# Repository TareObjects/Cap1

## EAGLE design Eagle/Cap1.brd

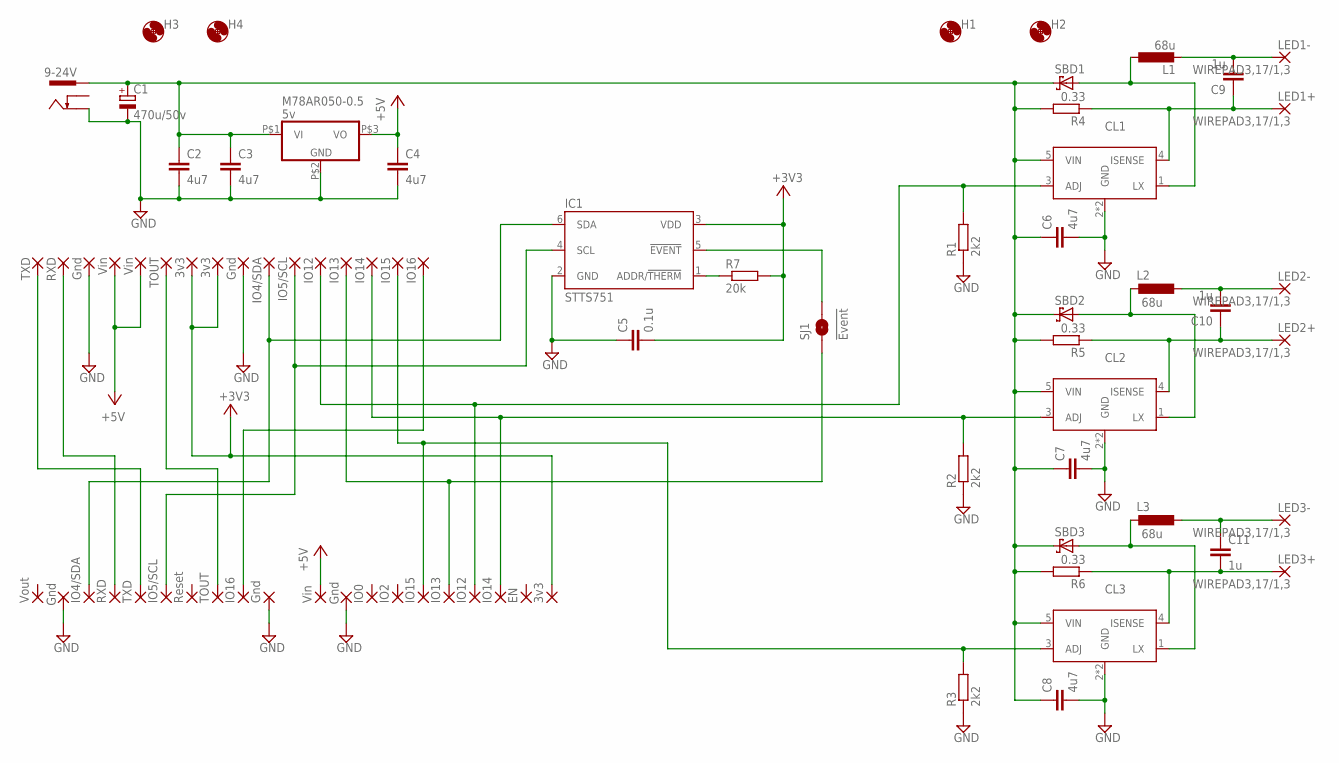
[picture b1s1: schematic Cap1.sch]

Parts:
0: IO0; 1,6/0,8
2: IO2; 1,6/0,8
3V, 3V3, 3V3': 3v3; 1,6/0,8
4: IO4/SDA; 1,6/0,8
5: IO5/SCL; 1,6/0,8
9-24V: DCJACK-MJ179P-R; MJ-179P-R
12: IO12; 1,6/0,8
13: IO13; 1,6/0,8
14: IO14; 1,6/0,8
15: IO15; 1,6/0,8
16: IO16; 1,6/0,8
C1: 470u/50v; E5-13
C2, C3, C4, C6, C7, C8: 4u7; C0805
C5: 0.1u; C0603
C9, C10, C11: 1u; C0603
CL1, CL2, CL3: CL6807; SOT89-5
EN: EN; 1,6/0,8
G: Gnd; 1,6/0,8
G': Gnd; 1,6/0,8
G'': Gnd; 1,6/0,8
GND, GND1: Gnd; 1,6/0,8
H1, H2, H3, H4: MOUNT-HOLE3.0; 3,0
IC1: STTS751; SOT23-6
IO4/SDA: IO4/SDA; 1,6/0,8
IO5/SCL: IO5/SCL; 1,6/0,8
IO12-CH1: IO12; 1,6/0,8
IO13': IO13; 1,6/0,8
IO14-CH2: IO14; 1,6/0,8
IO15-CH3: IO15; 1,6/0,8
IO16: IO16; 1,6/0,8
L1, L2, L3: 68u; NR10050
LED1+, LED1-, LED2+, LED2-, LED3+, LED3-: WIREPAD3,17/1,3; 3,17/1,3
M78AR050-0.5: 5v; M78AR
R1, R2, R3: 2k2; R0603
R4, R5, R6: 0.33; R3225
R7: 20k; R0603
RS: Reset; 1,6/0,8
RX: RXD; 1,6/0,8
RXD: RXD; 1,6/0,8
SBD1, SBD2, SBD3: SS2040FL2SS2040FL; SOD-123FL
SJ1: !Event; SJ_2S-NO
TO: TOUT; 1,6/0,8
TOUT: TOUT; 1,6/0,8
TX: TXD; 1,6/0,8
TXD: TXD; 1,6/0,8
VI: Vin; 1,6/0,8
VIN: Vin; 1,6/0,8
VIN': Vin; 1,6/0,8
VO: Vout; 1,6/0,8

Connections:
24VSUPPLY: 9-24V.1, C1.+, C2.1, C3.1, C6.1, C7.1, C8.1, CL1.5 (VIN), CL2.5 (VIN), CL3.5 (VIN), M78AR050-0.5.P$1 (VI), R4.2, R5.2, R6.2, SBD1.C, SBD2.C, SBD3.C
+3V3: 3V.1, 3V3.1, 3V3'.1, C5.2, IC1.3 (VDD), R7.2
+5V: C4.1, M78AR050-0.5.P$3 (VO), VI.1, VIN.1, VIN'.1
GND: 9-24V.2, C1.-, C2.2, C3.2, C4.2, C5.1, C6.2, C7.2, C8.2, CL1.2 (GND), CL1.2@TAB (GND), CL2.2 (GND), CL2.2@TAB (GND), CL3.2 (GND), CL3.2@TAB (GND), G.1, G'.1, G''.1, GND.1, GND1.1, IC1.2 (GND), M78AR050-0.5.P$2 (GND), R1.1, R2.1, R3.1
unnamed: RX.1, RXD.1
unnamed: TX.1, TXD.1
unnamed: TO.1, TOUT.1
unnamed: 15.1, CL3.3 (ADJ), IO15-CH3.1, R3.2
unnamed: IC1.1 (ADDR/!THERM), R7.1
unnamed: 13.1, IO13'.1, SJ1.1
unnamed: 4.1, IC1.6 (SDA), IO4/SDA.1
unnamed: 5.1, IC1.4 (SCL), IO5/SCL.1
unnamed: IC1.5 (!EVENT), SJ1.2
unnamed: 12.1, CL1.3 (ADJ), IO12-CH1.1, R1.2
unnamed: 14.1, CL2.3 (ADJ), IO14-CH2.1, R2.2
unnamed: C11.1, L3.P$2 (2), LED3-.1
unnamed: C9.1, CL1.4 (ISENSE), LED1+.1, R4.1
unnamed: CL1.1 (LX), L1.P$1 (1), SBD1.A
unnamed: C10.2, L2.P$2 (2), LED2-.1
unnamed: CL3.1 (LX), L3.P$1 (1), SBD3.A
unnamed: CL2.1 (LX), L2.P$1 (1), SBD2.A
unnamed: C10.1, CL2.4 (ISENSE), LED2+.1, R5.1
unnamed: C9.2, L1.P$2 (2), LED1-.1
unnamed: 16.1, IO16.1
unnamed: C11.2, CL3.4 (ISENSE), LED3+.1, R6.1

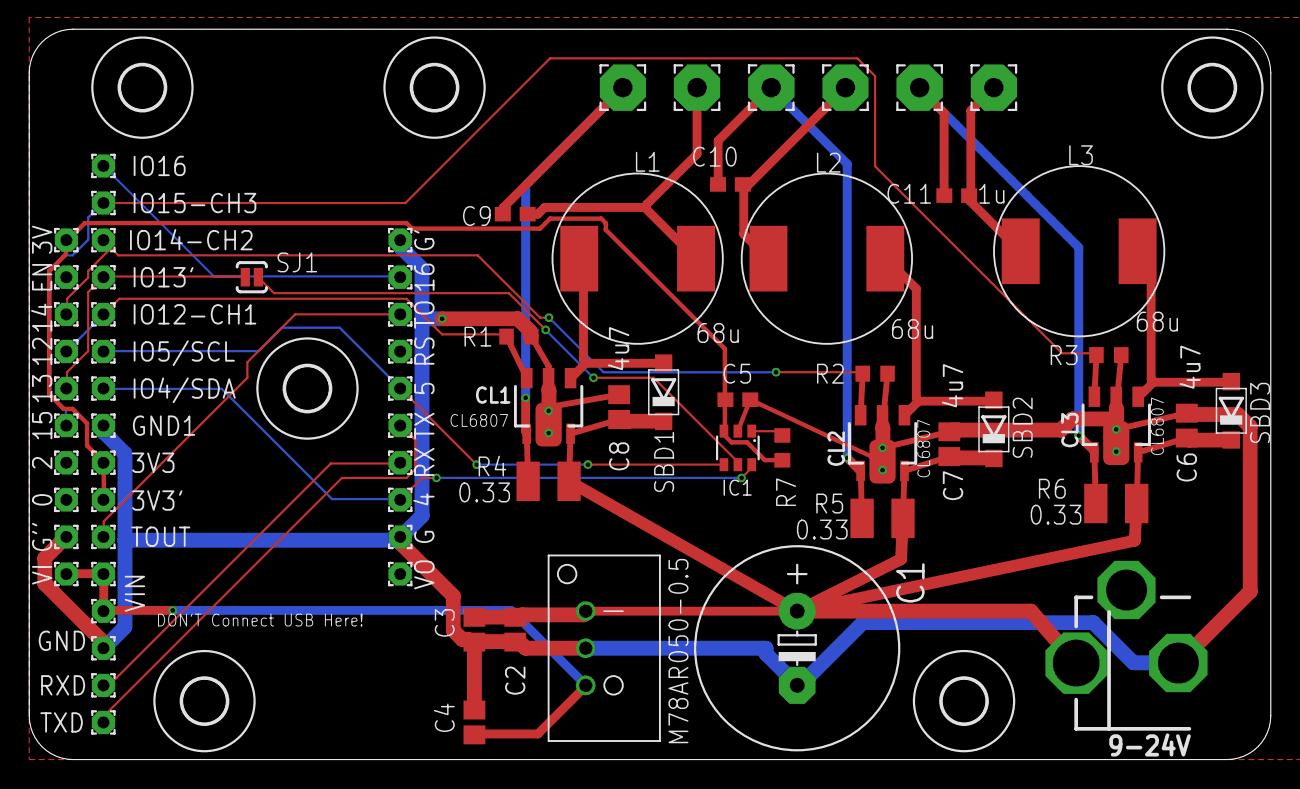
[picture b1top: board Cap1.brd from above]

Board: 2 copper layers, 85.0 x 50.0 mm, 79 parts (0 on the bottom side), 25 nets.

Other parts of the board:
H5, H6: MOUNT-HOLE3.0; 3,0

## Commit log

2017-03-10 回路とサンプルプログラム

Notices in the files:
parts and their libraries:
SparkFun: Licensing: CC v3.0 Share-Alike You are welcome to use this library for commercial purposes.
